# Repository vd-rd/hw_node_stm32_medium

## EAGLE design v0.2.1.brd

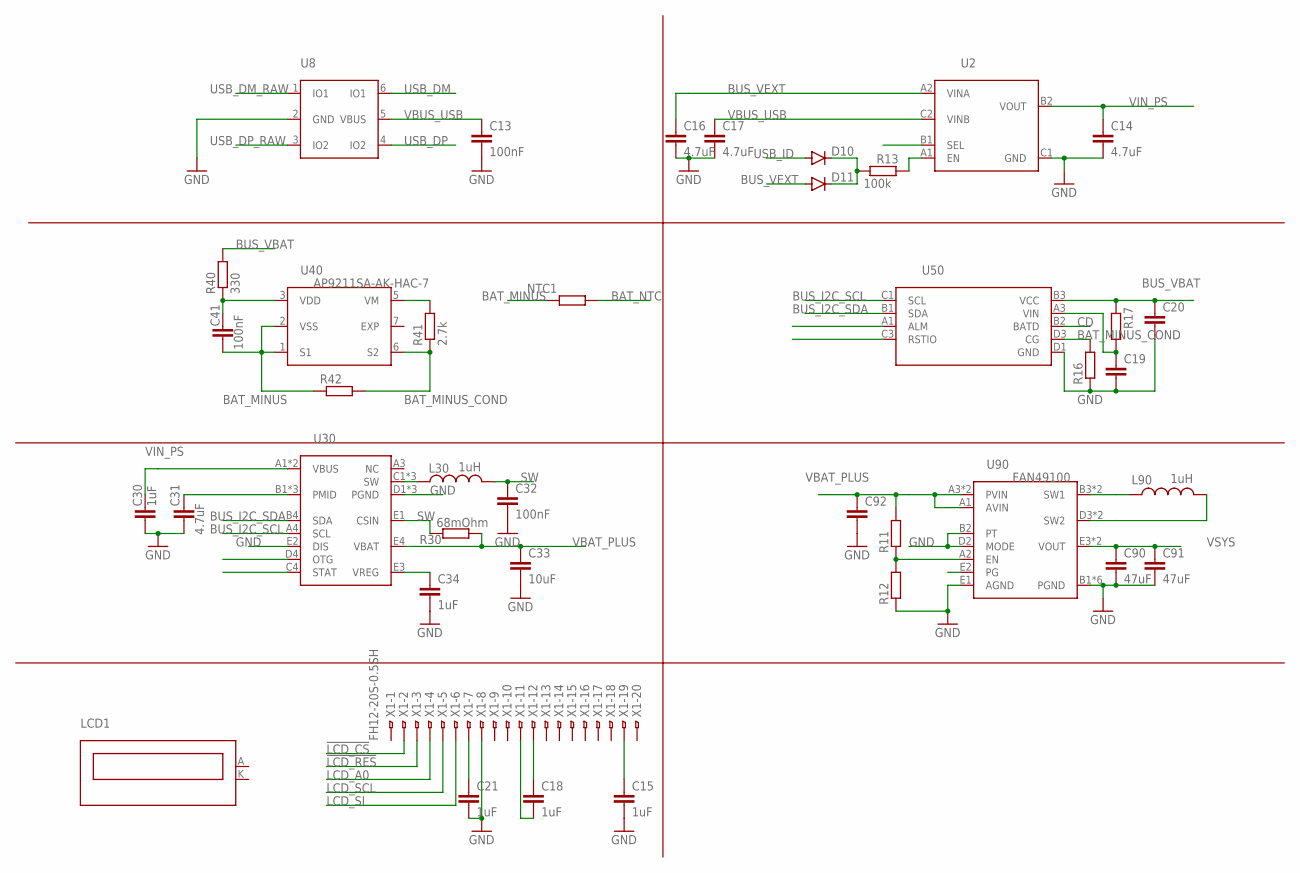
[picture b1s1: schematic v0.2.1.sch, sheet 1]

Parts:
C13, C32, C41: 100nF; C0402
C14, C16, C17, C31: 4.7uF; C0603
C15, C18: 1uF; C0805
C19, C20: C-EUC0402; C0402
C21: 1uF; C0603
C30, C34: 1uF; C0402
C33: 10uF; C0603
C90, C91: 47uF; C0805
C92: C-EUC0805; C0805
D10, D11: DIODE-SOD523; SOD523
L30, L90: 1uH; L3230M
LCD1: DEM-128064P-FGH-PW; DEM128064PFGH-PW
NTC1: R-EU_R0603; R0603
R11, R12, R17: R-EU_R0402; R0402
R13: 100k; R0402
R16: R-EU_R0805; R0805
R30: 68mOhm; R0805
R40: 330; R0402
R41: 2.7k; R0402
R42: R-EU_R0603; R0603
U2: FPF1320; BGA6C50P2X3_146X96X60
U8: USBLC6-2P6; SOTFL50P160X60-6
U30: FAN54015; BGA20C40P4X5_196X187X55
U40: AP9211SA-AK-HAC-7; DFN200X300X60-7N
U50: STC3115; BGA12C40P4X3_137X201X65
U90: FAN49100; BGA20C40P4X5_201X161X60
X1: FH12-20S-0.5SH

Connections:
!LCD_CS: X1.2
!LCD_RES: X1.3
BAT_MINUS: C41.2, NTC1.1, R42.1, U40.1 (S1), U40.2 (VSS)
BAT_MINUS_COND: R16.2, R41.1, R42.2, U40.6 (S2), U50.D3 (CG)
BAT_NTC: NTC1.2
BUS_I2C_SCL: U30.A4 (SCL), U50.C1 (SCL); also elsewhere on the board
BUS_I2C_SDA: U30.B4 (SDA), U50.B1 (SDA); also elsewhere on the board
BUS_VBAT: C20.1, R17.1, R40.2, U50.B3 (VCC); also elsewhere on the board
BUS_VEXT: C16.1, D11.A, U2.A2 (VINA); also elsewhere on the board
CD: U50.B2 (BATD)
EXP: U40.7 (EXP)
GND: C13.2, C14.2, C15.2, C16.2, C17.2, C19.2, C20.2, C21.2, C30.2, C31.2, C32.2, C33.2, C34.2, C90.2, C91.2, C92.2, R12.1, R16.1, U2.C1 (GND), U8.2 (GND), U30.D1 (PGND), U30.D2 (PGND), U30.D3 (PGND), U30.E2 (DIS), U50.D1 (GND), U90.B1 (PGND), U90.B2 (PT), U90.C1 (PGND), U90.C2 (PGND), U90.C3 (PGND), U90.C4 (PGND), U90.D1 (PGND), U90.D2 (MODE), U90.E1 (AGND), X1.8; also elsewhere on the board
LCD_A0: X1.4
LCD_SCL: X1.5
LCD_SI: X1.6
unnamed: C41.1, R40.1, U40.3 (VDD)
unnamed: D10.C, D11.C, R13.1
unnamed: R13.2, U2.A1 (EN)
unnamed: R41.2, U40.5 (VM)
unnamed: L30.1, U30.C1 (SW), U30.C2 (SW), U30.C3 (SW)
unnamed: C31.1, U30.B1 (PMID), U30.B2 (PMID), U30.B3 (PMID)
unnamed: L90.2, U90.D3 (SW2), U90.D4 (SW2)
unnamed: L90.1, U90.B3 (SW1), U90.B4 (SW1)
unnamed: C19.1, R17.2, U50.A3 (VIN)
unnamed: C34.1, U30.E3 (VREG)
unnamed: R11.1, R12.2, U90.A2 (EN)
unnamed: C21.1, X1.7
unnamed: C18.1, X1.12
unnamed: C18.2, X1.11
unnamed: C15.1, X1.19
SW: C32.1, L30.2, R30.1, U30.E1 (CSIN)
USB_DM: U8.6 (IO1); also elsewhere on the board
USB_DM_RAW: U8.1 (IO1); also elsewhere on the board
USB_DP: U8.4 (IO2); also elsewhere on the board
USB_DP_RAW: U8.3 (IO2); also elsewhere on the board
USB_ID: D10.A; also elsewhere on the board
VBAT_PLUS: C33.1, C92.1, R11.2, R30.2, U30.E4 (VBAT), U90.A1 (AVIN), U90.A3 (PVIN), U90.A4 (PVIN)
VBUS_USB: C13.1, C17.1, U2.C2 (VINB), U8.5 (VBUS); also elsewhere on the board
VIN_PS: C14.1, C30.1, U2.B2 (VOUT), U30.A1 (VBUS), U30.A2 (VBUS)
VSYS: C90.1, C91.1, U90.E3 (VOUT), U90.E4 (VOUT); also elsewhere on the board

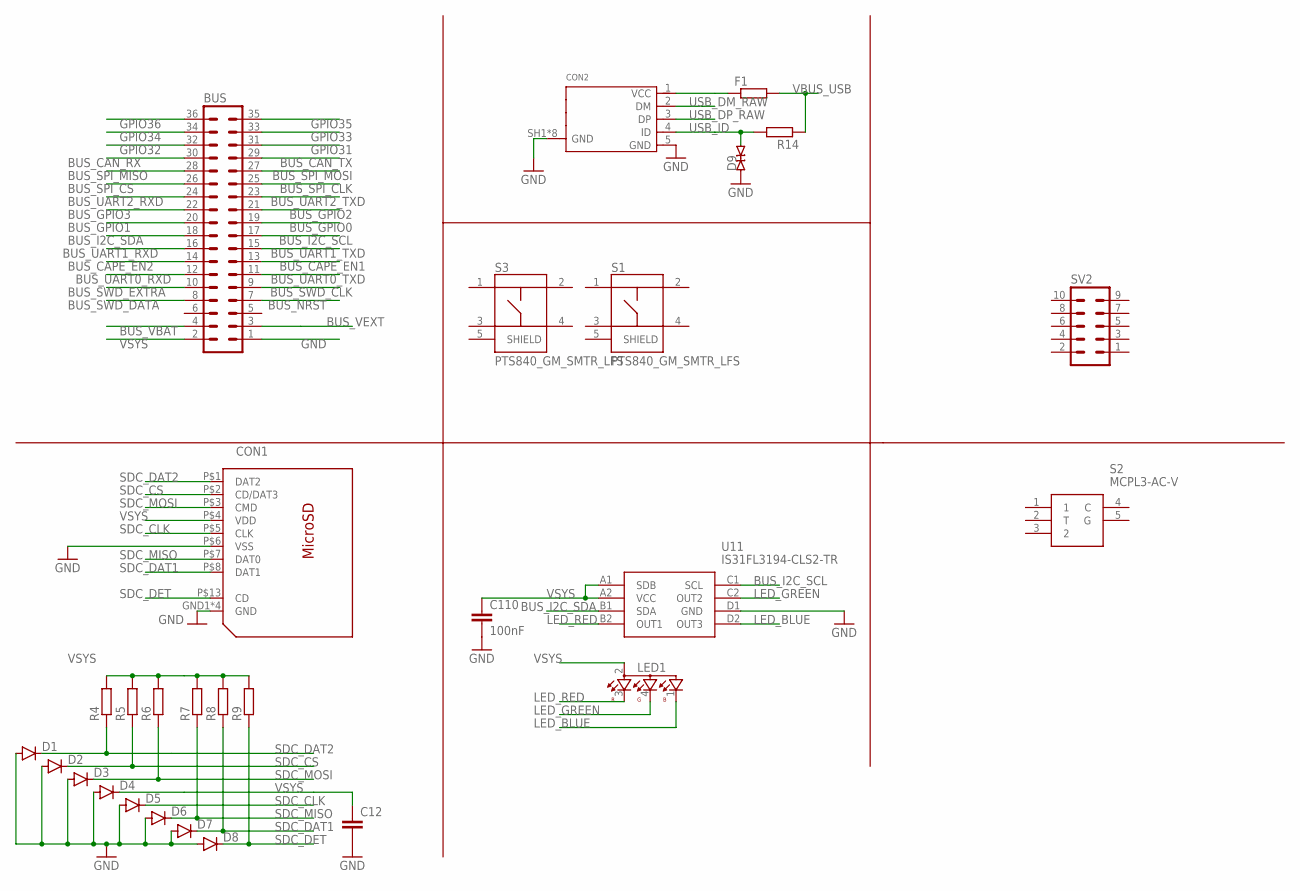
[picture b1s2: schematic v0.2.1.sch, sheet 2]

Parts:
BUS: MA18-2
C12: C-EUC0402; C0402
C110: 100nF; C0402
CON1: 112J-TXAR; 112J
CON2: 10118194-0001LF; 10118194
D1, D2, D3, D4, D5, D6, D7, D8: DIODE-SOD523; SOD523
D9: ESD9B5.0ST5G; SOD1006X40
F1: R-EU_R0603; R0603
LED1: OSTB1204C1E; 321015RGB
R4, R5, R6, R7, R8, R9, R14: R-EU_R0402; R0402
S1, S3: PTS840_GM_SMTR_LFS; SW_PTS840GMSMTRLFS
S2: MCPL3-AC-V
SV2: MA05-2
U11: IS31FL3194-CLS2-TR; BGA8C40P2X4_99X159X42

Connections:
BUS_CAN_RX: BUS.30
BUS_CAN_TX: BUS.29
BUS_CAPE_EN1: BUS.13; also elsewhere on the board
BUS_CAPE_EN2: BUS.14; also elsewhere on the board
BUS_GPIO0: BUS.19; also elsewhere on the board
BUS_GPIO1: BUS.20; also elsewhere on the board
BUS_GPIO2: BUS.21; also elsewhere on the board
BUS_GPIO3: BUS.22; also elsewhere on the board
BUS_I2C_SCL: BUS.17, U11.C1 (SCL); also elsewhere on the board
BUS_I2C_SDA: BUS.18, U11.B1 (SDA); also elsewhere on the board
BUS_NRST: BUS.7; also elsewhere on the board
BUS_SPI_CLK: BUS.25; also elsewhere on the board
BUS_SPI_CS: BUS.26; also elsewhere on the board
BUS_SPI_MISO: BUS.28; also elsewhere on the board
BUS_SPI_MOSI: BUS.27; also elsewhere on the board
BUS_SWD_CLK: BUS.9; also elsewhere on the board
BUS_SWD_DATA: BUS.8; also elsewhere on the board
BUS_SWD_EXTRA: BUS.10
BUS_UART0_RXD: BUS.12; also elsewhere on the board
BUS_UART0_TXD: BUS.11; also elsewhere on the board
BUS_UART1_RXD: BUS.16; also elsewhere on the board
BUS_UART1_TXD: BUS.15; also elsewhere on the board
BUS_UART2_RXD: BUS.24; also elsewhere on the board
BUS_UART2_TXD: BUS.23; also elsewhere on the board
BUS_VBAT: BUS.4; also elsewhere on the board
BUS_VEXT: BUS.3; also elsewhere on the board
GND: BUS.1, C12.2, C110.2, CON1.GND1 (GND), CON1.GND2 (GND), CON1.GND3 (GND), CON1.GND4 (GND), CON1.P$6 (VSS), CON2.5 (GND), CON2.SH1 (GND), CON2.SH2 (GND), CON2.SH3 (GND), CON2.SH4 (GND), CON2.SH5 (GND), CON2.SH6 (GND), CON2.SH7 (GND), CON2.SH8 (GND), D1.A, D2.A, D3.A, D4.A, D5.A, D6.A, D7.A, D8.A, D9.1 (A), U11.D1 (GND); also elsewhere on the board
GPIO31: BUS.31; also elsewhere on the board
GPIO32: BUS.32; also elsewhere on the board
GPIO33: BUS.33; also elsewhere on the board
GPIO34: BUS.34; also elsewhere on the board
GPIO35: BUS.35; also elsewhere on the board
GPIO36: BUS.36; also elsewhere on the board
LED_BLUE: LED1.1, U11.D2 (OUT3)
LED_GREEN: LED1.4, U11.C2 (OUT2)
LED_RED: LED1.3, U11.B2 (OUT1)
unnamed: CON2.1 (VCC), F1.1
SDC_CLK: CON1.P$5 (CLK), D5.C; also elsewhere on the board
SDC_CS: CON1.P$2 (CD/DAT3), D2.C, R5.1; also elsewhere on the board
SDC_DAT1: CON1.P$8 (DAT1), D7.C, R8.1
SDC_DAT2: CON1.P$1 (DAT2), D1.C, R4.1
SDC_DET: CON1.P$13 (CD), D8.C, R9.1
SDC_MISO: CON1.P$7 (DAT0), D6.C, R7.1; also elsewhere on the board
SDC_MOSI: CON1.P$3 (CMD), D3.C, R6.1; also elsewhere on the board
USB_DM_RAW: CON2.2 (DM); also elsewhere on the board
USB_DP_RAW: CON2.3 (DP); also elsewhere on the board
USB_ID: CON2.4 (ID), D9.2 (C), R14.2; also elsewhere on the board
VBUS_USB: F1.2, R14.1; also elsewhere on the board
VSYS: BUS.2, C12.1, C110.1, CON1.P$4 (VDD), D4.C, LED1.2, R4.2, R5.2, R6.2, R7.2, R8.2, R9.2, U11.A1 (SDB), U11.A2 (VCC); also elsewhere on the board

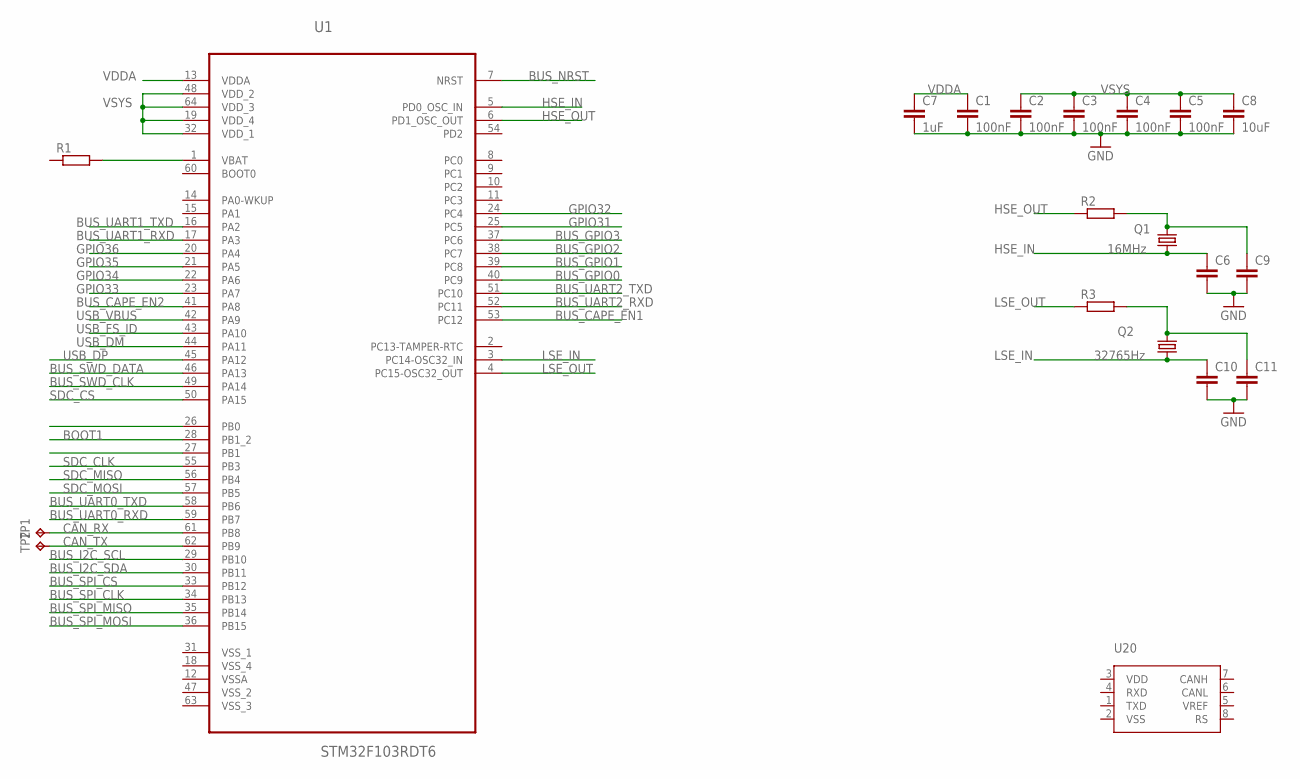
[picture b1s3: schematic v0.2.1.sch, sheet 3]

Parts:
C1, C2, C3, C4, C5: 100nF; C0402
C6, C9, C10, C11: C-EUC0402; C0402
C7: 1uF; C0402
C8: 10uF; C0603
Q1: 16MHz; 3.2X2.5_KX-7
Q2: 32765Hz; 3.2X1.5
R1, R2, R3: R-EU_R0402; R0402
TP1, TP2: TPB1,27; B1,27
U1: STM32F103RDT6; QFP50P1200X1200X160-64N
U20: MCP2551; SOIC8

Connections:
BOOT1: U1.28 (PB1_2)
BUS_CAPE_EN1: U1.53 (PC12); also elsewhere on the board
BUS_CAPE_EN2: U1.41 (PA8); also elsewhere on the board
BUS_GPIO0: U1.40 (PC9); also elsewhere on the board
BUS_GPIO1: U1.39 (PC8); also elsewhere on the board
BUS_GPIO2: U1.38 (PC7); also elsewhere on the board
BUS_GPIO3: U1.37 (PC6); also elsewhere on the board
BUS_I2C_SCL: U1.29 (PB10); also elsewhere on the board
BUS_I2C_SDA: U1.30 (PB11); also elsewhere on the board
BUS_NRST: U1.7 (NRST); also elsewhere on the board
BUS_SPI_CLK: U1.34 (PB13); also elsewhere on the board
BUS_SPI_CS: U1.33 (PB12); also elsewhere on the board
BUS_SPI_MISO: U1.35 (PB14); also elsewhere on the board
BUS_SPI_MOSI: U1.36 (PB15); also elsewhere on the board
BUS_SWD_CLK: U1.49 (PA14); also elsewhere on the board
BUS_SWD_DATA: U1.46 (PA13); also elsewhere on the board
BUS_UART0_RXD: U1.59 (PB7); also elsewhere on the board
BUS_UART0_TXD: U1.58 (PB6); also elsewhere on the board
BUS_UART1_RXD: U1.17 (PA3); also elsewhere on the board
BUS_UART1_TXD: U1.16 (PA2); also elsewhere on the board
BUS_UART2_RXD: U1.52 (PC11); also elsewhere on the board
BUS_UART2_TXD: U1.51 (PC10); also elsewhere on the board
CAN_RX: TP1.TP, U1.61 (PB8)
CAN_TX: TP2.TP, U1.62 (PB9)
GND: C1.2, C2.2, C3.2, C4.2, C5.2, C6.2, C7.2, C8.2, C9.2, C10.2, C11.2; also elsewhere on the board
GPIO31: U1.25 (PC5); also elsewhere on the board
GPIO32: U1.24 (PC4); also elsewhere on the board
GPIO33: U1.23 (PA7); also elsewhere on the board
GPIO34: U1.22 (PA6); also elsewhere on the board
GPIO35: U1.21 (PA5); also elsewhere on the board
GPIO36: U1.20 (PA4); also elsewhere on the board
HSE_IN: C6.1, Q1.1, U1.5 (PD0_OSC_IN)
HSE_OUT: R2.1, U1.6 (PD1_OSC_OUT)
LSE_IN: C10.1, Q2.1, U1.3 (PC14-OSC32_IN)
LSE_OUT: R3.1, U1.4 (PC15-OSC32_OUT)
unnamed: R1.2, U1.1 (VBAT)
unnamed: C9.1, Q1.3 (2), R2.2
unnamed: C11.1, Q2.2, R3.2
SDC_CLK: U1.55 (PB3); also elsewhere on the board
SDC_CS: U1.50 (PA15); also elsewhere on the board
SDC_MISO: U1.56 (PB4); also elsewhere on the board
SDC_MOSI: U1.57 (PB5); also elsewhere on the board
USB_DM: U1.44 (PA11); also elsewhere on the board
USB_DP: U1.45 (PA12); also elsewhere on the board
USB_FS_ID: U1.43 (PA10)
USB_VBUS: U1.42 (PA9)
VDDA: C1.1, C7.1, U1.13 (VDDA)
VSYS: C2.1, C3.1, C4.1, C5.1, C8.1, U1.19 (VDD_4), U1.32 (VDD_1), U1.48 (VDD_2), U1.64 (VDD_3); also elsewhere on the board

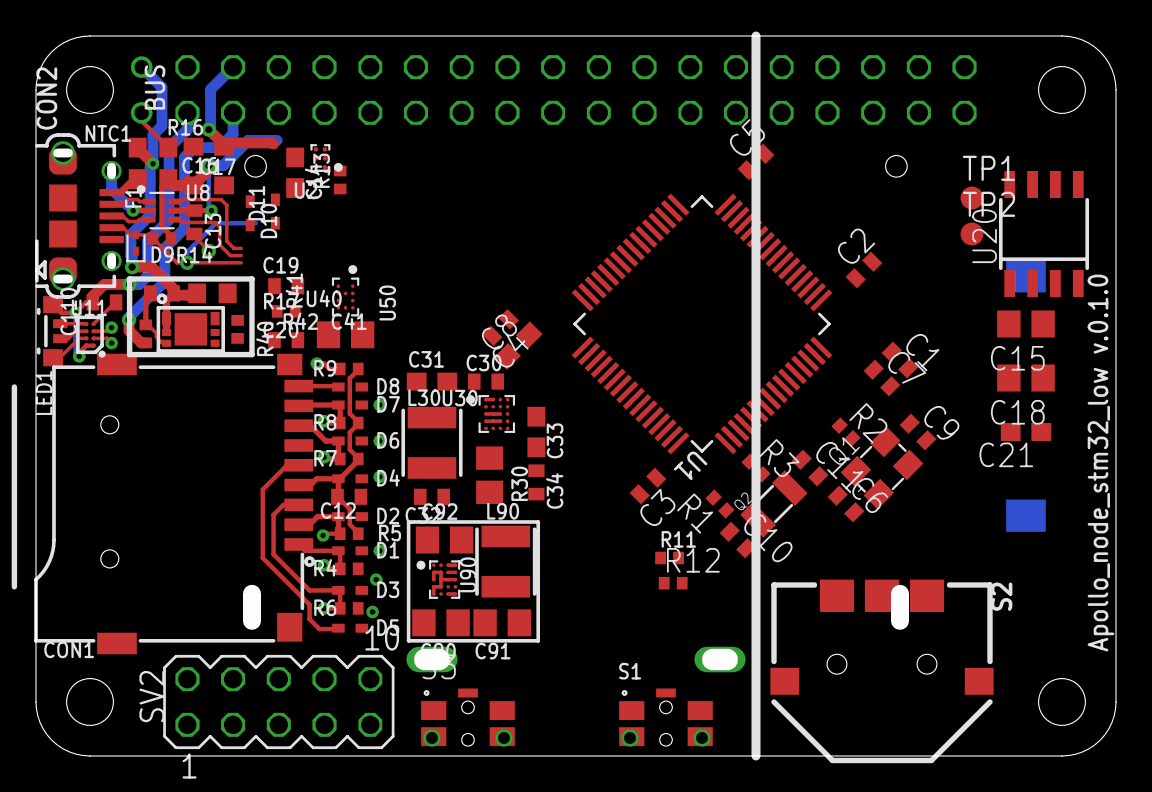
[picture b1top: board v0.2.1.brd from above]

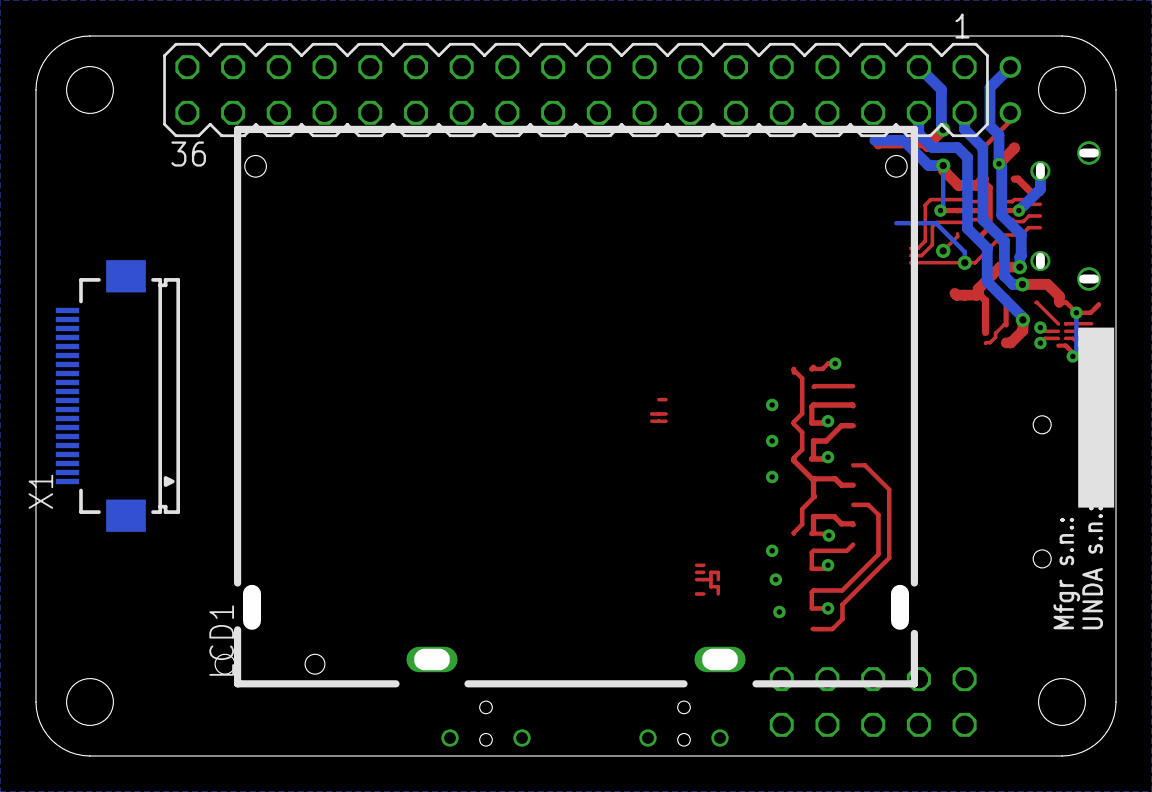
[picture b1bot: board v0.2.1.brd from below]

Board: 2 copper layers, 60.0 x 40.0 mm, 88 parts (3 on the bottom side), 78 nets.

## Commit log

2018-12-20 board bringup
2018-12-20 added clocks and power filtering
2018-12-29 finished interconnect pin description
2018-12-30 defined pinout for stm32
2018-12-30 bus definition completed
2019-01-09 floorplan update
2019-01-14 added power stage
2019-01-20 updated footprints and 3d models
2019-01-22 added 3d models
2019-02-06 cosmetic fixes
2019-03-02 modified schematics
2019-05-02 project: structure update

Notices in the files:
parts and their libraries:
crystal-geyer_V1_0: Copyright: Geyer-Electronic
